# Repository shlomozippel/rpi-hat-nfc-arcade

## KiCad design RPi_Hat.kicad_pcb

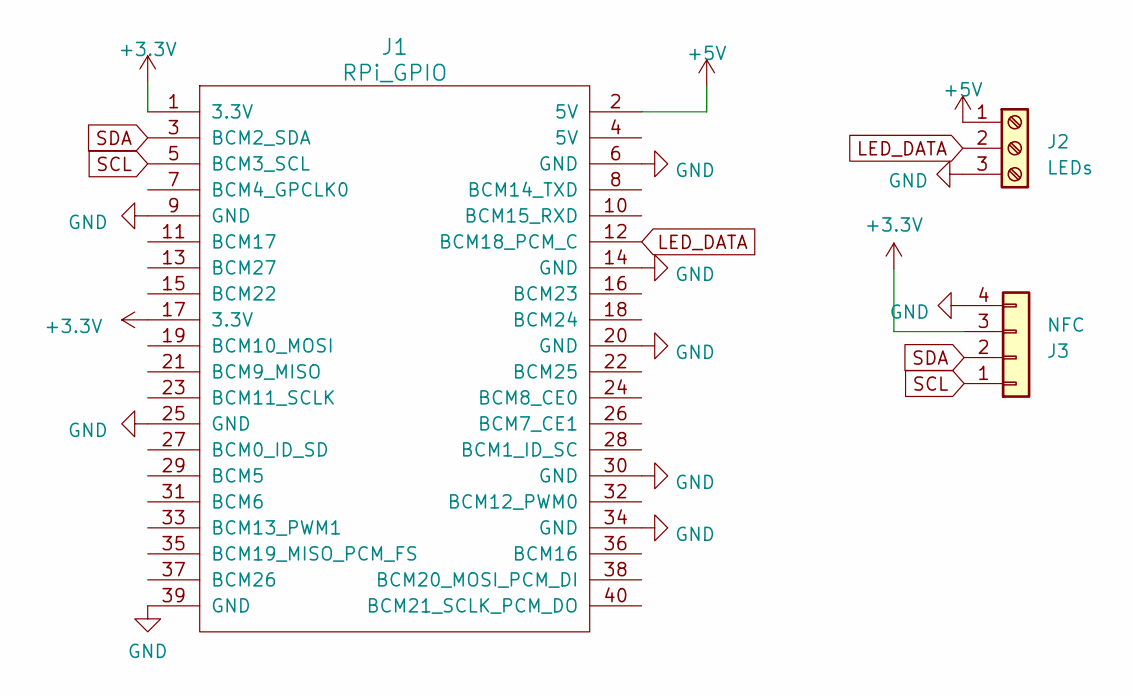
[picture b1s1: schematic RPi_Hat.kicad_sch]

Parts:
J1: RPi_GPIO; PinSocket_2x20_P2.54mm_Vertical; LCSC C5124634
J2: LEDs; PinHeader_1x03_P2.54mm_Vertical; LCSC C474921
J3: NFC; PinHeader_1x04_P2.54mm_Horizontal; LCSC C7501292

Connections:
+3.3V: J1.1 (3.3V), J1.17 (3.3V), J3.3
+5V: J1.2 (5V), J2.1
GND: J1.6 (GND), J1.9 (GND), J1.14 (GND), J1.20 (GND), J1.25 (GND), J1.30 (GND), J1.34 (GND), J1.39 (GND), J2.3, J3.4
LED_DATA: J1.12 (BCM18_PCM_C), J2.2
SCL: J1.5 (BCM3_SCL), J3.1
SDA: J1.3 (BCM2_SDA), J3.2

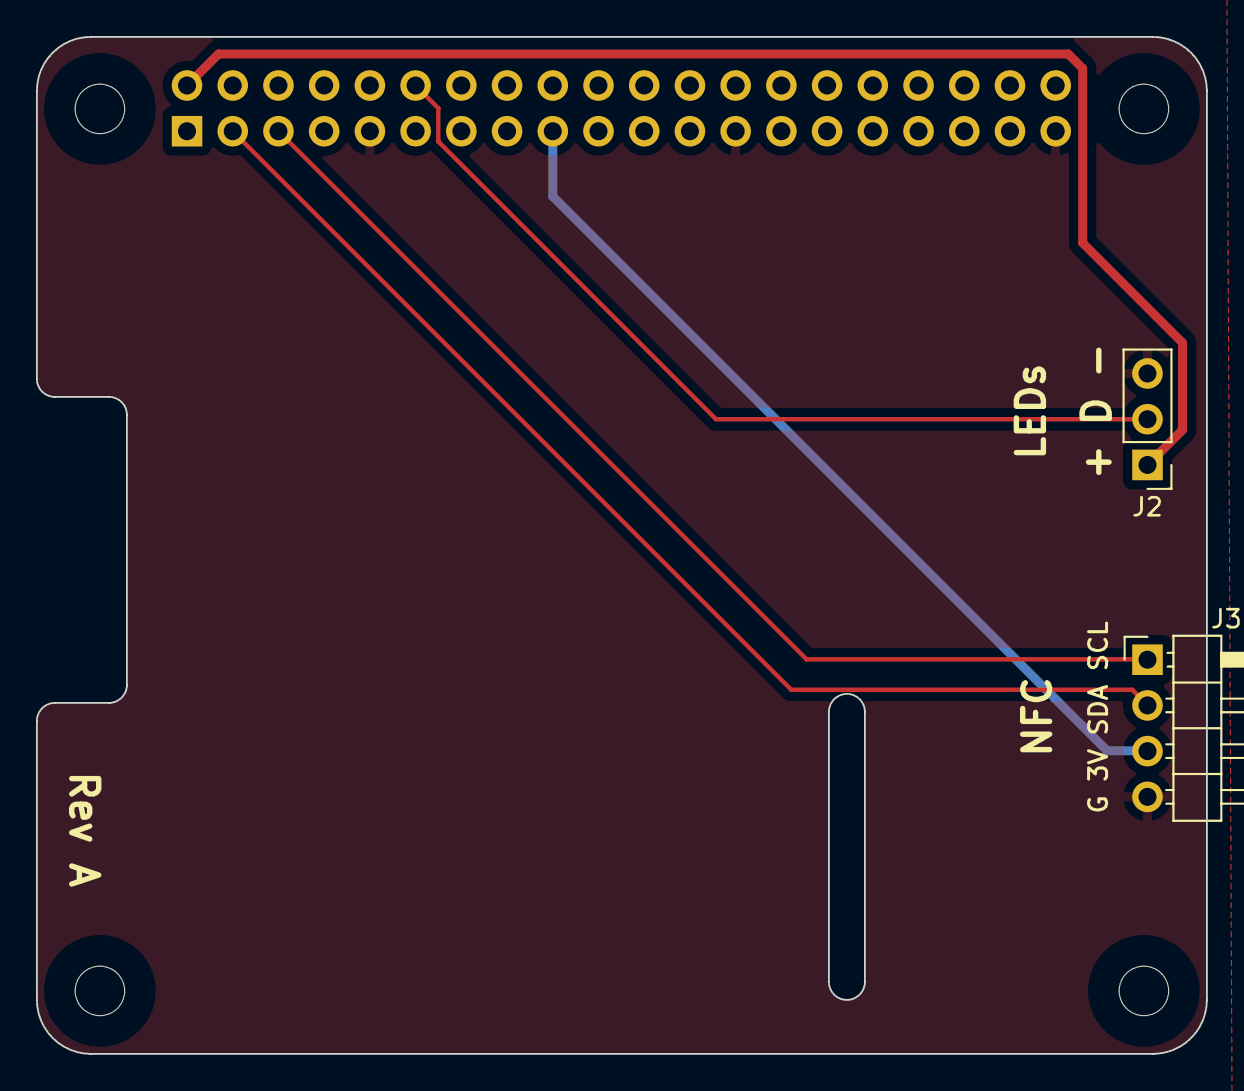
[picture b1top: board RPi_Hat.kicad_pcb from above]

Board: 2 copper layers, 65.0 x 56.5 mm, 3 parts (1 on the bottom side), 6 nets.

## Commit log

2024-03-02 added missing files
